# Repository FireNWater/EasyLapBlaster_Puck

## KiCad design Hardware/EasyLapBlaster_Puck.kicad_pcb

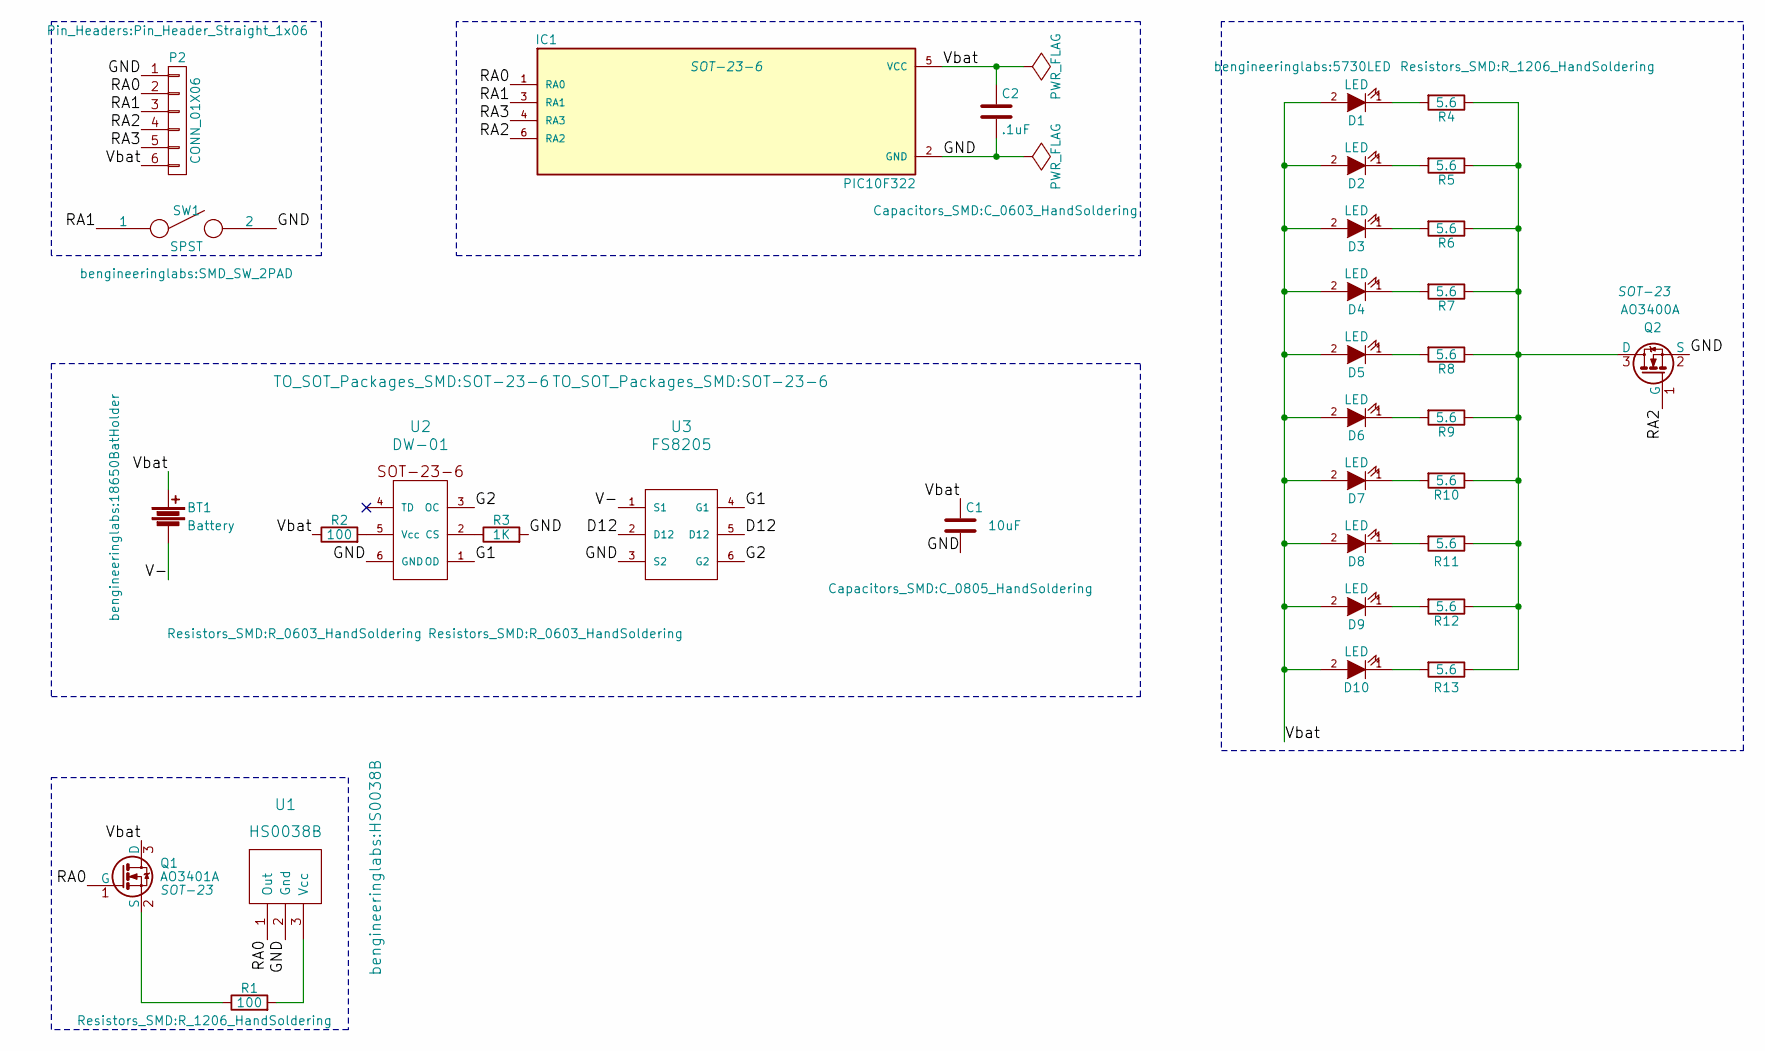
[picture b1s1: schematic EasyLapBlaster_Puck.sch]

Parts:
BT1: Battery; 18650BatHolder
C1: 10uF; C_0805_HandSoldering
C2: .1uF; C_0603_HandSoldering
D1, D2, D3, D4, D5, D6, D7, D8, D9, D10: LED; 5730LED
IC1: PIC10F322; SOT-23-6
P2: CONN_01X06; Pin_Header_Straight_1x06
Q1: AO3401A; SOT-23
Q2: AO3400A; SOT-23
R1: 100; R_1206_HandSoldering
R2: 100; R_0603_HandSoldering
R3: 1K; R_0603_HandSoldering
R4, R5, R6, R7, R8, R9, R10, R11, R12, R13: 5.6; R_1206_HandSoldering
SW1: SPST; SMD_SW_2PAD
U1: HS0038B
U2: DW-01; SOT-23-6
U3: FS8205; SOT-23-6

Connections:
/D12: U3.2 (D12), U3.5 (D12)
/G1: U2.1 (OD), U3.4 (G1)
/G2: U2.3 (OC), U3.6 (G2)
/GND: C1.2, C2.2, IC1.2 (GND), P2.1, Q2.2 (S), R3.2, SW1.2, U1.2 (Gnd), U2.6 (GND), U3.3 (S2)
/RA0: IC1.1 (RA0), P2.2, Q1.1 (G), U1.1 (Out)
/RA1: IC1.3 (RA1), P2.3, SW1.1
/RA2: IC1.6 (RA2), P2.4, Q2.1 (G)
/RA3: IC1.4 (RA3), P2.5
/V-: BT1.2, U3.1 (S1)
/Vbat: BT1.1, C1.1, C2.1, D1.2 (A), D2.2 (A), D3.2 (A), D4.2 (A), D5.2 (A), D6.2 (A), D7.2 (A), D8.2 (A), D9.2 (A), D10.2 (A), IC1.5 (VCC), P2.6, Q1.3 (D), R2.1
unnamed: D1.1 (K), R4.2
unnamed: D2.1 (K), R5.2
unnamed: D3.1 (K), R6.2
unnamed: D4.1 (K), R7.2
unnamed: D5.1 (K), R8.2
unnamed: D6.1 (K), R9.2
unnamed: D7.1 (K), R10.2
unnamed: D8.1 (K), R11.2
unnamed: D9.1 (K), R12.2
unnamed: D10.1 (K), R13.2
unnamed: Q1.2 (S), R1.1
unnamed: Q2.3 (D), R4.1, R5.1, R6.1, R7.1, R8.1, R9.1, R10.1, R11.1, R12.1, R13.1
unnamed: R1.2, U1.3 (Vcc)
unnamed: R2.2, U2.5 (Vcc)
unnamed: R3.1, U2.2 (CS)

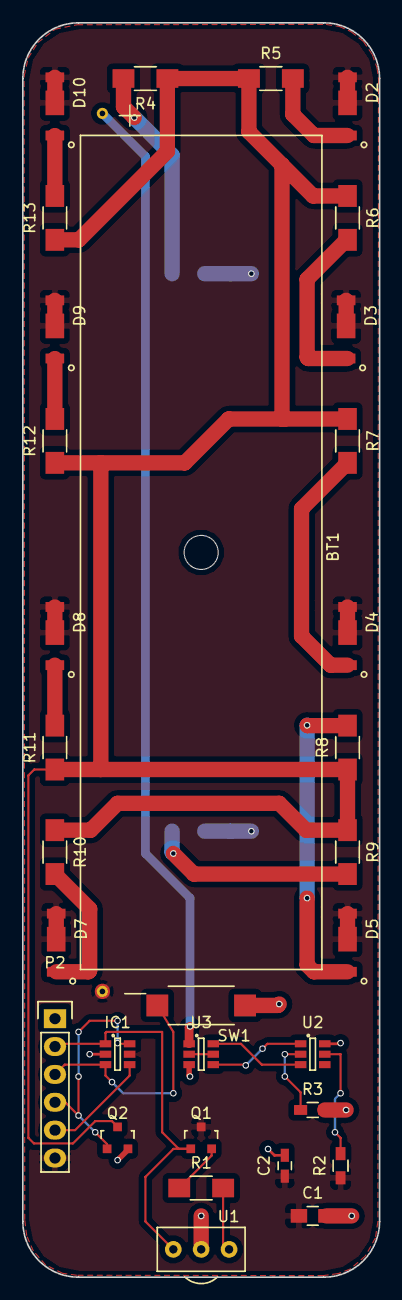
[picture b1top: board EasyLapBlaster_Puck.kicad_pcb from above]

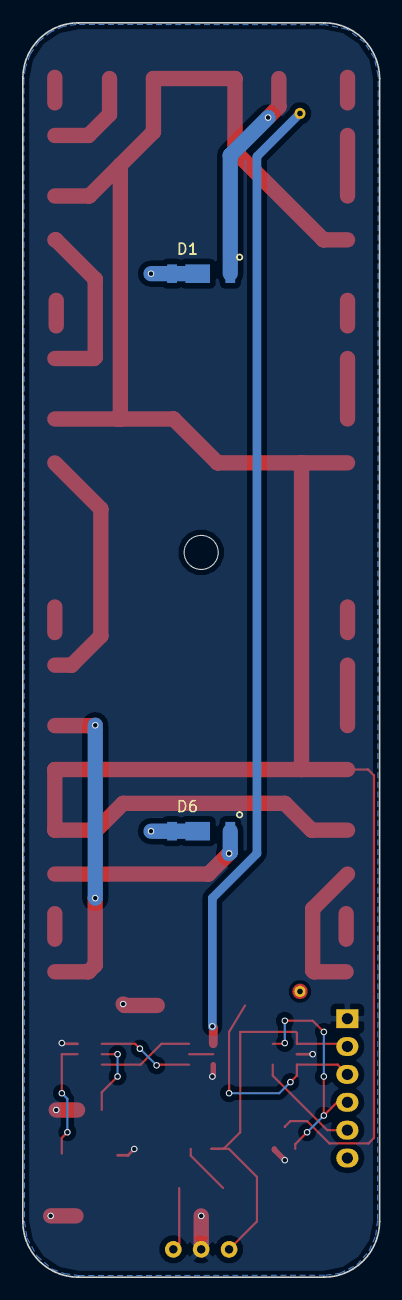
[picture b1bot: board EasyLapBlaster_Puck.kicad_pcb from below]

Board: 2 copper layers, 32.5 x 114.3 mm, 34 parts (2 on the bottom side), 25 nets.

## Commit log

2016-06-14 Initial File Upload
2016-06-15 Did some house cleaning on file structure
2016-06-15 Adding back moved files
2016-06-15 Continued moving folders, added init project for pic firmware
2016-06-15 Added footprint for SMD switch
2016-06-15 Adding MPLAB project files
2016-06-15 added LED footprint, rearranged led/resistor order for better heatsinking (VCC can be poured on the top layer)
2016-06-17 added footprint for HS0038B
2016-06-17 added 18650 footprint, added to schematic
2016-06-17 netlist updated on board file, layout is still a mess
2016-06-22 Keith's Changes: Slimmed down board, organized components added .gitattributes & .gitignore
2016-06-28 Added power traces.
    Need to widen board and Vcc/Gnd fill areas.
2016-06-29 Widened board slightly and finished traces.
    Widened board by about 4mm to allow Vbat zone to reach all of the LED's.
    Finished all traces. Ready for QC
